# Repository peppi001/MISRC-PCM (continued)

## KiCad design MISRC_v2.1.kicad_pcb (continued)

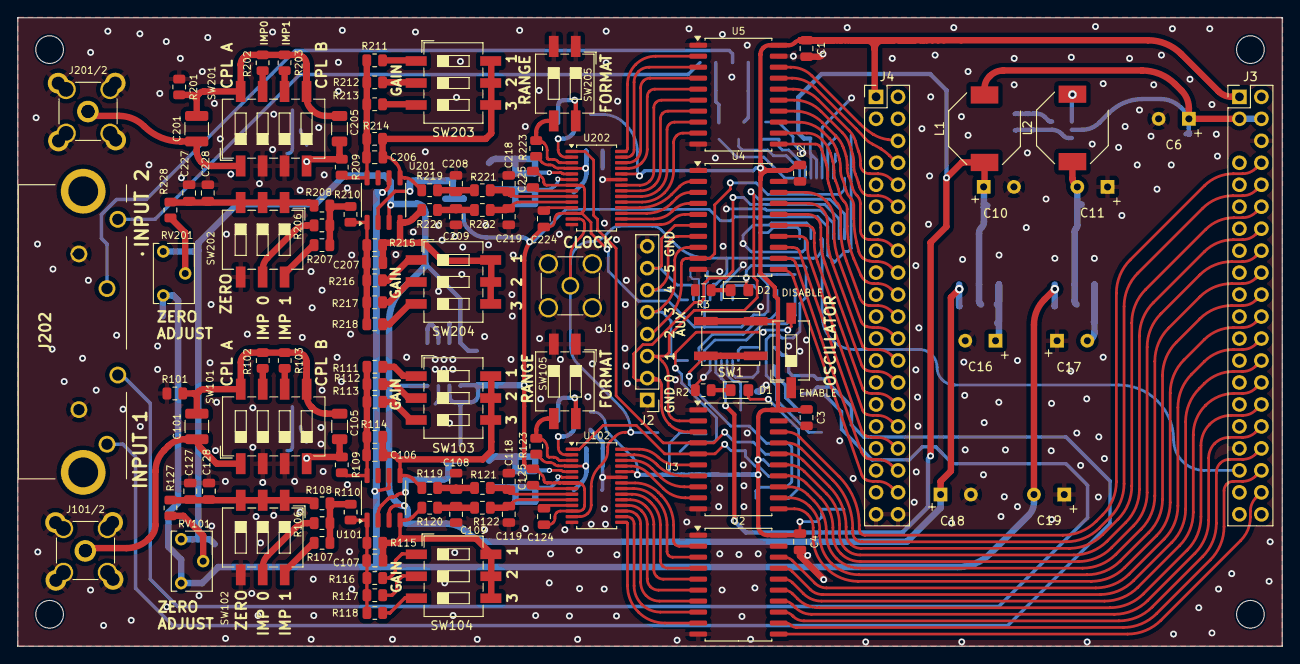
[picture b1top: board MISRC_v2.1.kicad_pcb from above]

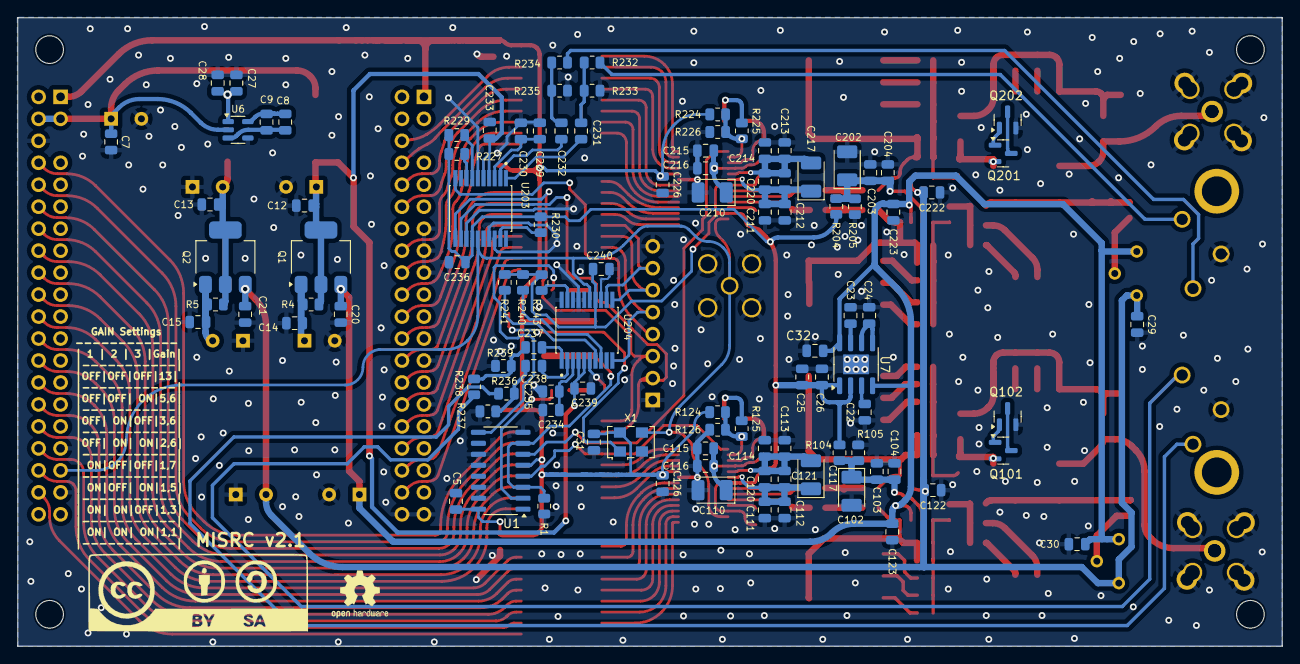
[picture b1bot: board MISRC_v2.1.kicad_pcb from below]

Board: 2 copper layers, 146.2 x 72.6 mm, 224 parts (104 on the bottom side), 173 nets.

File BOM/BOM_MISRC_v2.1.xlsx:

Reference | Value | Footprint | Qty | DNP | Manufacturer_Part_Number
C1,C2,C3,C4,C5,C7,C12,C13,C20,C21,C22,C23,C24,C29,C30,C31,C231,C232,C237,C238 | 1u | Capacitor_SMD:C_0805_2012Metric | 20 |  | GRM219R61H105KA73D
C6,C10,C11,C16,C17,C18,C19 | 470u | CP_Radial_Flat_D8.0mm_P3.50mm | 7 |  | UHV1C471MPD
C8,C25,C28,C32,C127,C227,C229,C234 | 10u | Capacitor_SMD:C_0805_2012Metric | 8 |  | GRM21BR61C106KE15K
C9,C14,C15,C26,C103,C112,C113,C115,C120,C122,C123,C124,C125,C126,C203,C212,C213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 | 100n | Capacitor_SMD:C_0805_2012Metric | 30 |  | GRM21BR72A104KAC4L
C27,C104,C111,C114,C116,C121,C128,C204,C211,C214,C216,C221,C228 | 1n/1 | Capacitor_SMD:C_0805_2012Metric | 13 |  | GRM2195C1H102JA01D
C101,C201 | 100u | Capacitor_SMD:C_1210_3225Metric | 2 |  | GRM32ER61A107ME20K
C102,C110,C117,C202,C210,C217 | 10u | Capacitor_Tantalum_SMD:CP_EIA-3528-21_Kemet-B_Pad1.50x2.35mm_HandSolder | 6 |  | T491B106K016AT7280
C105,C205 | 470n/1 | Capacitor_SMD:C_1206_3216Metric | 2 |  | GRM31C5C1E474JE01L
C106,C107,C206,C207 | 1p | Capacitor_SMD:C_0805_2012Metric | 4 | DNP
C108,C109,C208,C209 | 82pF/1 | Capacitor_SMD:C_0805_2012Metric | 4 |  | GRM21A5C2D820JW01D
C118,C119,C218,C219 | 15pF/1 | Capacitor_SMD:C_0805_2012Metric | 4 |  | GRM21A5C2D150JW01D
D1,D2 | LED | LED_SMD:LED_0805_2012Metric_Pad1.15x1.40mm_HandSolder | 2 |  | APT2012EC
H1,H2,H3,H4 | MountingHole | MountingHole:MountingHole_3.2mm_M3 | 4 | DNP
J1 | Conn_01x01_Shielded | Footprints:SMA_Amphenol_901-144_Vertical2 | 1 |  | RF2-04A-T-00-50-G
J2 | Conn_01x08_Socket | Connector_PinHeader_2.54mm:PinHeader_1x08_P2.54mm_Vertical | 1 | DNP | 61300811121
J3 | GPIFII_J6 | Footprints:PinHeader_2x20_P2.54mm_Vertical-1 | 1 |  | 61302021121
J4 | GPIFII_J7 | Footprints:PinHeader_2x20_P2.54mm_Vertical-1 | 1 |  | 61302021121
J101,J201 | BNC_Rosenberger | Footprints:BNC Socket_mod | 2 | DNP | DOSIN-801-0050
J101/2,J201/2 | Conn_01x01_Shielded | Footprints:SMA_Amphenol_901-144_Horizontal | 2 |  | CONSMA002-L-G
J202 | KLP42X-61-WW_RR | KLP42X61WWRR | 1 |  | KLP42X-61-WW/RR
L1,L2 | 100u | Footprints:L_Bourns-SRU8043_2 | 2 |  | SRU8043-101Y
Q1 | FZT690B | Package_TO_SOT_SMD:SOT-223-3_TabPin2 | 1 |  | FZT690BTA
Q2 | FZT790A | Package_TO_SOT_SMD:SOT-223-3_TabPin2 | 1 |  | FZT790A
Q101,Q102,Q201,Q202 | CMPT5179 | Package_TO_SOT_SMD:SOT-23 | 4 |  | CMPT5179 TR PBFREE
R1,R123,R126,R223,R226,R232,R234,R236,R238 | 10k | Resistor_SMD:R_0805_2012Metric | 9 |  | RC0805FR-0710KL
R2,R3 | 100 | Resistor_SMD:R_0805_2012Metric | 2 |  | RC0805FR-07100RL
R4,R5,R227,R229,R230,R240,R241,R243 | 1k | Resistor_SMD:R_0805_2012Metric | 8 |  | RT0805BRD071KL
R101,R103,R106,R201,R203,R206 | 75B | Resistor_SMD:R_0805_2012Metric | 6 |  | RT0805BRD0775RL
R102,R202 | 150B | Resistor_SMD:R_0805_2012Metric | 2 |  | RT0805BRD07150RL
R104,R105,R111,R116,R204,R205,R211,R216 | 1kB | Resistor_SMD:R_0805_2012Metric | 8 |  | RT0805BRD071KL
R107,R108,R207,R208 | 39B | Resistor_SMD:R_0805_2012Metric | 4 |  | RT0805BRD0739RL
R109,R110,R209,R210 | 499B | Resistor_SMD:R_0805_2012Metric | 4 |  | RT0805BRD07499RL
R112,R117,R212,R217 | 2k49B | Resistor_SMD:R_0805_2012Metric | 4 |  | RT0805BRD072K49L
R113,R118,R213,R218 | 4k99B | Resistor_SMD:R_0805_2012Metric | 4 |  | RT0805BRD074K99L
R114,R115,R214,R215 | 6k49B | Resistor_SMD:R_0805_2012Metric | 4 |  | RT0805BRD076K49L
R119,R120,R219,R220 | 40B | Resistor_SMD:R_0805_2012Metric | 4 |  | RT0805BRD0739R2L
R121,R122,R221,R222 | 22B | Resistor_SMD:R_0805_2012Metric | 4 |  | RT0805BRD0722RL
R124,R224 | 4k99 | Resistor_SMD:R_0805_2012Metric | 2 |  | RC0805FR-074K99L
R125,R127,R225,R228 | 3k3 | Resistor_SMD:R_0805_2012Metric | 4 |  | RC0805FR-073K3L
R233,R235,R237,R239 | 47k | Resistor_SMD:R_0805_2012Metric | 4 |  | RC0805FR-0747KL
RV101,RV201 | 10k | Potentiometer_THT:Potentiometer_Bourns_3266W_Vertical | 2 |  | 3266W-1-103LF
SW1 | SW_Push | Footprints:SW_SPST_EVQP0_2 | 1 |  | B3FS-1010P
SW2 | SW_DIP_x01 | Button_Switch_SMD:SW_DIP_SPSTx01_Slide_6.7x4.1mm_W8.61mm_P2.54mm_LowProfile | 1 |  | EDS01SGRSTR04Q
SW101,SW201 | SW_DIP_x04 | Button_Switch_SMD:SW_DIP_SPSTx04_Slide_6.7x11.72mm_W8.61mm_P2.54mm_LowProfile | 2 |  | IKD0403101
SW102,SW103,SW104,SW202,SW203,SW204 | SW_DIP_x03 | Button_Switch_SMD:SW_DIP_SPSTx03_Slide_6.7x9.18mm_W8.61mm_P2.54mm_LowProfile | 6 |  | A6S-3104-H
SW105,SW205 | SW_DIP_x02 | Button_Switch_SMD:SW_DIP_SPSTx02_Slide_6.7x6.64mm_W8.61mm_P2.54mm_LowProfile | 2 |  | IKD0203101
U1 | 4043 | Package_SO:SO-16_3.9x9.9mm_P1.27mm | 1 |  | HEF4043BT-Q100J
U2,U3,U4,U5 | 74VHC541 | Package_SO:SOIC-20W_7.5x12.8mm_P1.27mm | 4 |  | 74VHC541D,118
U6 | TPS60401 | Package_TO_SOT_SMD:SOT-23-5 | 1 |  | TPS60401DBVT
U7 | ADP7156ARDZ | Footprints:SOIC-8-1EP_3.9x4.9mm_P1.27mm_EP2.29x3mm_2 | 1 |  | ADP7156ARDZ-3.3-R7
U101,U201 | AD8138ARZ | Package_SO:SO-8_3.9x4.9mm_P1.27mm | 2 |  | AD8138ARZ
U102,U202 | AD9235 | Package_SO:TSSOP-28_4.4x9.7mm_P0.65mm | 2 |  | AD9235BRUZ-40
U203,U204 | PCM1802DBR | Footprints:SOP65P780X200-20N | 2 |  | PCM1802DBR
X1 | 40M | Oscillator:Oscillator_SMD_EuroQuartz_XO53-4Pin_5.0x3.2mm | 1 |  | ECS-5032MV-400-CN-TR

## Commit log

2024-05-23 Replace BNC connector
    Replace BNC connector and change PCB size to "original" MISRC
2024-05-23 Update silkscreen
    Update bottom side silkscreen
